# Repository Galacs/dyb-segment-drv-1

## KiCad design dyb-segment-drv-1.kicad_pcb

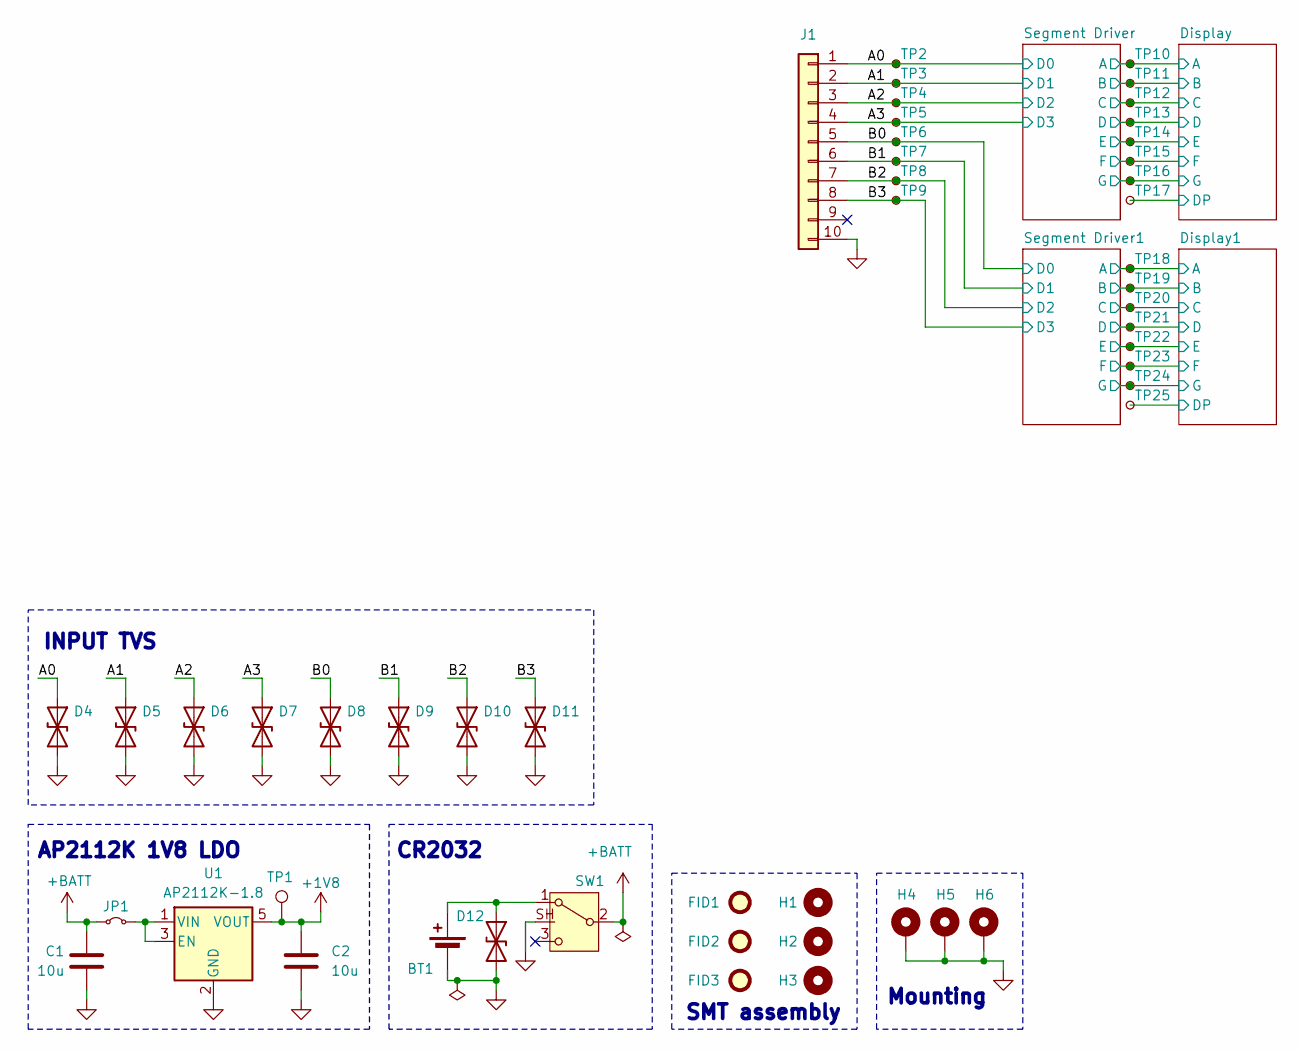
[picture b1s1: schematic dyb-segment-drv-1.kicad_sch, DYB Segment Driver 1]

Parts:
BT1: Battery_Cell; BatteryHolder_MYOUNG_BS-08-B2AA016; Manufacturer Part Number BS-08-B2AA016; JLCPCB Part # C964792
C1, C2: 10u; C_0805_2012Metric; Manufacturer Part Number GRM21BR61H106KE43L; JLCPCB Part # C440198
D4, D5, D6, D7, D8, D9, D10, D11, D12: H3V3L10B; Diode_DFN1006; Manufacturer Part Number H3V3L10B; JLCPCB Part # C20615781
FID1, FID2, FID3: Fiducial; Fiducial_1mm_Mask2mm
H1, H2, H3: MountingHole; ToolingHole_1.152mm
H4, H5, H6: MountingHole_Pad; MountingHole_3.2mm_M3_Pad_Via
J1: Conn_01x10; KYOCERA_AVX9159-006
JP1: Jumper_2_Small_Bridged; PinHeader_1x02_P2.54mm_Horizontal
SW1: SW_SPDT; SW_SPDT_Shouhan_MSK12C02; Manufacturer Part Number MSK12C02; JLCPCB Part # C431540
TP1: TestPoint; TestPoint_Pad_D1.0mm
TP2, TP3, TP4, TP5, TP6, TP7, TP8, TP9, TP10, TP11, TP12, TP13, TP14, TP15, TP16, TP17, TP18, TP19, TP20, TP21, TP22, TP23, TP24, TP25: TestPoint_Small; TestPoint_Pad_D1.0mm
U1: AP2112K-1.8; SOT-23-5; Manufacturer Part Number AP2112K-1.8TRG1; JLCPCB Part # C176944

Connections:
+1V8: C2.1, TP1.1 (1_1), U1.5 (VOUT); also elsewhere on the board
/A0: D4.1 (A1), J1.1, TP2.1 (1_1); also elsewhere on the board
/A1: D5.1 (A1), J1.2, TP3.1 (1_1); also elsewhere on the board
/A2: D6.1 (A1), J1.3, TP4.1 (1_1); also elsewhere on the board
/A3: D7.1 (A1), J1.4, TP5.1 (1_1); also elsewhere on the board
/B0: D8.1 (A1), J1.5, TP6.1 (1_1); also elsewhere on the board
/B1: D9.1 (A1), J1.6, TP7.1 (1_1); also elsewhere on the board
/B2: D10.1 (A1), J1.7, TP8.1 (1_1); also elsewhere on the board
/B3: D11.1 (A1), J1.8, TP9.1 (1_1); also elsewhere on the board
/Display1/A: TP18.1 (1_1); also elsewhere on the board
/Display1/B: TP19.1 (1_1); also elsewhere on the board
/Display1/C: TP20.1 (1_1); also elsewhere on the board
/Display1/D: TP21.1 (1_1); also elsewhere on the board
/Display1/DP: TP25.1 (1_1); also elsewhere on the board
/Display1/E: TP22.1 (1_1); also elsewhere on the board
/Display1/F: TP23.1 (1_1); also elsewhere on the board
/Display1/G: TP24.1 (1_1); also elsewhere on the board
/Display/A: TP10.1 (1_1); also elsewhere on the board
/Display/B: TP11.1 (1_1); also elsewhere on the board
/Display/C: TP12.1 (1_1); also elsewhere on the board
/Display/D: TP13.1 (1_1); also elsewhere on the board
/Display/DP: TP17.1 (1_1); also elsewhere on the board
/Display/E: TP14.1 (1_1); also elsewhere on the board
/Display/F: TP15.1 (1_1); also elsewhere on the board
/Display/G: TP16.1 (1_1); also elsewhere on the board
GND: BT1.2 (-), C1.2, C2.2, D4.2 (A2), D5.2 (A2), D6.2 (A2), D7.2 (A2), D8.2 (A2), D9.2 (A2), D10.2 (A2), D11.2 (A2), D12.2 (A2), H4.1 (1_1), H5.1 (1_1), H6.1 (1_1), J1.10, SW1.SH, U1.2 (GND); also elsewhere on the board
unnamed: BT1.1 (+), D12.1 (A1), SW1.1 (A)

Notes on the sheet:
SMT assembly
INPUT TVS
Mounting
AP2112K 1V8 LDO
CR2032

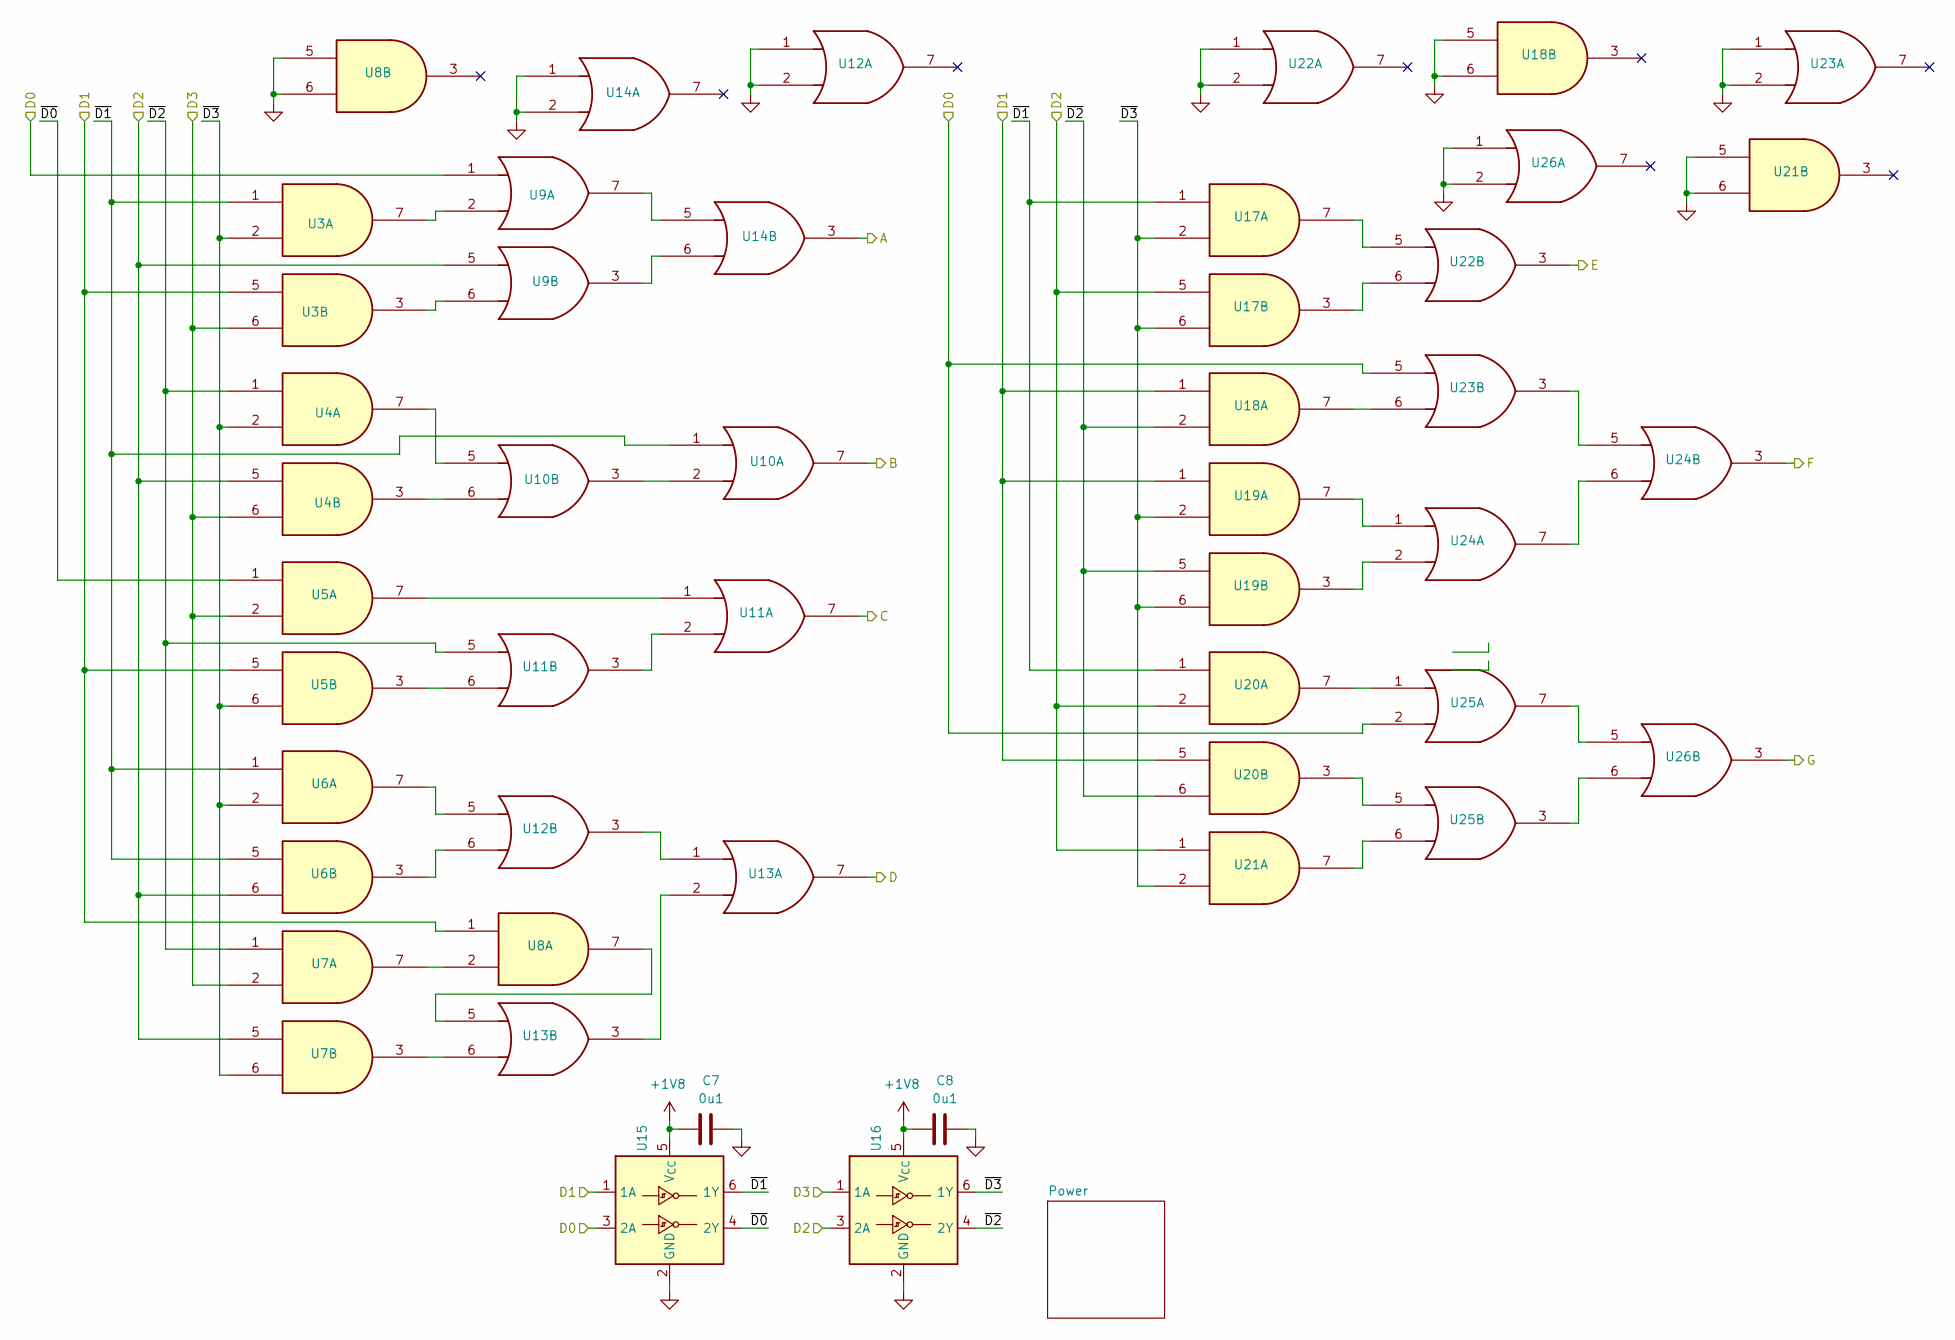
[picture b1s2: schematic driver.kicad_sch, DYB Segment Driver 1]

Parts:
C7, C8: 0u1; C_0402_1005Metric; Manufacturer Part Number CL05B104KB54PNC; JLCPCB Part # C307331
U3, U4, U5, U6, U7, U8, U17, U18, U19, U20, U21: SN74AUP2G08; VSSOP-8_2.3x2mm_P0.5mm; Manufacturer Part Number SN74AUP2G08DCUR; JLCPCB Part # C544478
U9, U10, U11, U12, U13, U14, U22, U23, U24, U25, U26: 74AUC2G32; VSSOP-8_2.3x2mm_P0.5mm; Manufacturer Part Number SN74AUP2G32DCUR; JLCPCB Part # C2876519
U15, U16: Inverter_Schmitt_Dual; SOT-363_SC-70-6; Manufacturer Part Number SN74AUP2G14DCKR; JLCPCB Part # C139318

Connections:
+1V8: C7.1, C8.1, U15.5 (V_{CC}), U16.5 (V_{CC}); also elsewhere on the board
/A0: U9.1, U15.3 (2A), U23.5, U25.2; also elsewhere on the board
/A1: U3.5, U5.5, U8.1, U15.1 (1A), U18.1, U19.1, U20.5; also elsewhere on the board
/A2: U4.5, U6.6, U7.5, U9.5, U16.3 (2A), U17.5, U20.2, U21.1; also elsewhere on the board
/A3: U3.6, U4.6, U5.2, U7.2, U16.1 (1A); also elsewhere on the board
/Display/A: U14.3; also elsewhere on the board
/Display/B: U10.7; also elsewhere on the board
/Display/C: U11.7; also elsewhere on the board
/Display/D: U13.7; also elsewhere on the board
/Display/E: U22.3; also elsewhere on the board
/Display/F: U24.3; also elsewhere on the board
/Display/G: U26.3; also elsewhere on the board
/Segment Driver/~D0: U5.1, U15.4 (2Y)
/Segment Driver/~D1: U3.1, U6.1, U6.5, U10.1, U15.6 (1Y), U17.1, U20.1
/Segment Driver/~D2: U4.1, U7.1, U11.5, U16.4 (2Y), U18.2, U19.5, U20.6
/Segment Driver/~D3: U3.2, U4.2, U5.6, U6.2, U7.6, U16.6 (1Y), U17.2, U17.6, U19.2, U19.6, U21.2
GND: C7.2, C8.2, U8.5, U8.6, U12.1, U12.2, U14.1, U14.2, U15.2 (GND), U16.2 (GND), U18.5, U18.6, U21.5, U21.6, U22.1, U22.2, U23.1, U23.2, U26.1, U26.2; also elsewhere on the board
unnamed: U3.3, U9.6
unnamed: U3.7, U9.2
unnamed: U7.7, U8.2
unnamed: U10.2, U10.3
unnamed: U4.7, U10.5
unnamed: U4.3, U10.6
unnamed: U5.7, U11.1
unnamed: U11.2, U11.3
unnamed: U5.3, U11.6
unnamed: U12.3, U13.1
unnamed: U6.7, U12.5
unnamed: U6.3, U12.6
unnamed: U13.2, U13.3
unnamed: U8.7, U13.5
unnamed: U7.3, U13.6
unnamed: U9.7, U14.5
unnamed: U9.3, U14.6
unnamed: U17.3, U22.6
unnamed: U17.7, U22.5
unnamed: U18.7, U23.6
unnamed: U19.3, U24.2
unnamed: U19.7, U24.1
unnamed: U20.3, U25.5
unnamed: U20.7, U25.1
unnamed: U21.7, U25.6
unnamed: U23.3, U24.5
unnamed: U24.6, U24.7
unnamed: U25.3, U26.6
unnamed: U25.7, U26.5

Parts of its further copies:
C35, C36: 0u1; C_0402_1005Metric; Manufacturer Part Number CL05B104KB54PNC; JLCPCB Part # C307331
U28, U29, U30, U31, U32, U33, U42, U43, U44, U45, U46: SN74AUP2G08; VSSOP-8_2.3x2mm_P0.5mm; Manufacturer Part Number SN74AUP2G08DCUR; JLCPCB Part # C544478
U34, U35, U36, U37, U38, U39, U47, U48, U49, U50, U51: 74AUC2G32; VSSOP-8_2.3x2mm_P0.5mm; Manufacturer Part Number SN74AUP2G32DCUR; JLCPCB Part # C2876519
U40, U41: Inverter_Schmitt_Dual; SOT-363_SC-70-6; Manufacturer Part Number SN74AUP2G14DCKR; JLCPCB Part # C139318

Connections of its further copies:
+1V8: C35.1, C36.1, U28.8 (VCC), U29.8 (VCC), U30.8 (VCC), U31.8 (VCC), U32.8 (VCC), U33.8 (VCC), U34.8 (VCC), U35.8 (VCC), U36.8 (VCC), U37.8 (VCC), U38.8 (VCC), U39.8 (VCC), U40.5 (V_{CC}), U41.5 (V_{CC}), U42.8 (VCC), U43.8 (VCC), U44.8 (VCC), U45.8 (VCC), U46.8 (VCC), U47.8 (VCC), U48.8 (VCC), U49.8 (VCC), U50.8 (VCC), U51.8 (VCC); also elsewhere on the board
/B0: U34.1, U40.3 (2A), U48.5, U50.2; also elsewhere on the board
/B1: U28.5, U30.5, U33.1, U40.1 (1A), U43.1, U44.1, U45.5; also elsewhere on the board
/B2: U29.5, U31.6, U32.5, U34.5, U41.3 (2A), U42.5, U45.2, U46.1; also elsewhere on the board
/B3: U28.6, U29.6, U30.2, U32.2, U41.1 (1A); also elsewhere on the board
/Display1/A: U39.3; also elsewhere on the board
/Display1/B: U35.7; also elsewhere on the board
/Display1/C: U36.7; also elsewhere on the board
/Display1/D: U38.7; also elsewhere on the board
/Display1/E: U47.3; also elsewhere on the board
/Display1/F: U49.3; also elsewhere on the board
/Display1/G: U51.3; also elsewhere on the board
/Segment Driver1/~D0: U30.1, U40.4 (2Y)
/Segment Driver1/~D1: U28.1, U31.1, U31.5, U35.1, U40.6 (1Y), U42.1, U45.1
/Segment Driver1/~D2: U29.1, U32.1, U36.5, U41.4 (2Y), U43.2, U44.5, U45.6
/Segment Driver1/~D3: U28.2, U29.2, U30.6, U31.2, U32.6, U41.6 (1Y), U42.2, U42.6, U44.2, U44.6, U46.2
GND: C35.2, C36.2, U28.4 (GND), U29.4 (GND), U30.4 (GND), U31.4 (GND), U32.4 (GND), U33.4 (GND), U33.5, U33.6, U34.4 (GND), U35.4 (GND), U36.4 (GND), U37.1, U37.2, U37.4 (GND), U38.4 (GND), U39.1, U39.2, U39.4 (GND), U40.2 (GND), U41.2 (GND), U42.4 (GND), U43.4 (GND), U43.5, U43.6, U44.4 (GND), U45.4 (GND), U46.4 (GND), U46.5, U46.6, U47.1, U47.2, U47.4 (GND), U48.1, U48.2, U48.4 (GND), U49.4 (GND), U50.4 (GND), U51.1, U51.2, U51.4 (GND); also elsewhere on the board
unnamed: U28.3, U34.6
unnamed: U28.7, U34.2
unnamed: U29.3, U35.6
unnamed: U29.7, U35.5
unnamed: U30.3, U36.6
unnamed: U30.7, U36.1
unnamed: U31.3, U37.6
unnamed: U31.7, U37.5
unnamed: U32.3, U38.6
unnamed: U32.7, U33.2
unnamed: U33.7, U38.5
unnamed: U34.3, U39.6
unnamed: U34.7, U39.5
unnamed: U35.2, U35.3
unnamed: U36.2, U36.3
unnamed: U37.3, U38.1
unnamed: U38.2, U38.3
unnamed: U42.3, U47.6
unnamed: U42.7, U47.5
unnamed: U43.7, U48.6
unnamed: U44.3, U49.2
unnamed: U44.7, U49.1
unnamed: U45.3, U50.5
unnamed: U45.7, U50.1
unnamed: U46.7, U50.6
unnamed: U48.3, U49.5
unnamed: U49.6, U49.7
unnamed: U50.3, U51.6
unnamed: U50.7, U51.5

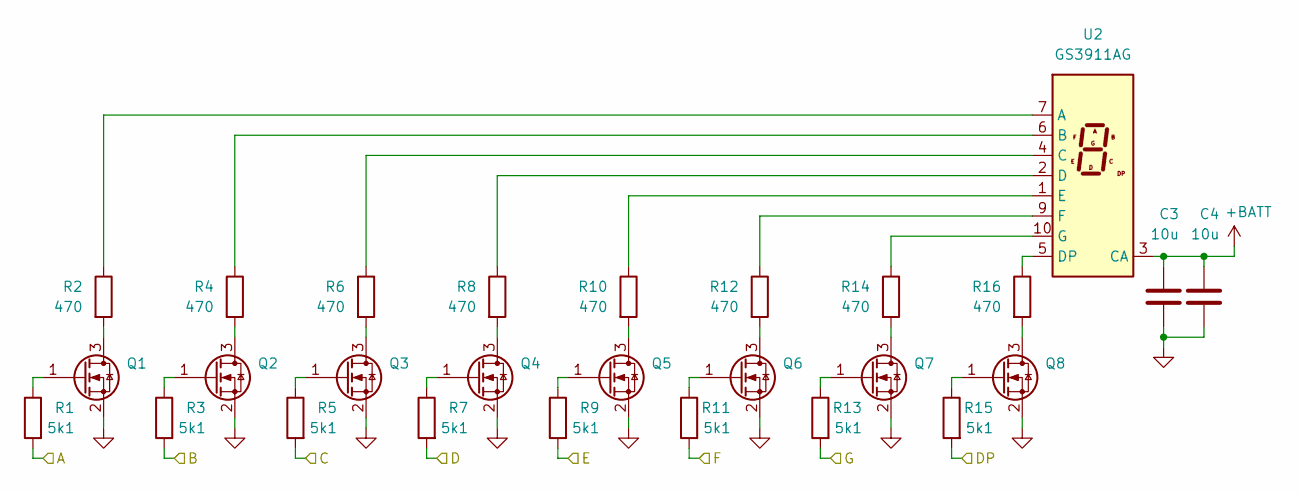
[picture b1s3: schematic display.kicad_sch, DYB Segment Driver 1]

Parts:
C3, C4: 10u; C_0805_2012Metric; Manufacturer Part Number GRM21BR61H106KE43L; JLCPCB Part # C440198
Q1, Q2, Q3, Q4, Q5, Q6, Q7, Q8: HL2300; SOT-23; Manufacturer Part Number HL2300; JLCPCB Part # C7420343
R1, R3, R5, R7, R9, R11, R13, R15: 5k1; R_0402_1005Metric; Manufacturer Part Number 0402WGF5101TCE; JLCPCB Part # C25905
R2, R4, R6, R8, R10, R12, R14, R16: 470; R_0402_1005Metric; Manufacturer Part Number 0402WGF4700TCE; JLCPCB Part # C25117
U2: GS3911AG; Manufacturer Part Number GS3911AG-G; JLCPCB Part # C22462667

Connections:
/Display/A: R1.2; also elsewhere on the board
/Display/B: R3.2; also elsewhere on the board
/Display/C: R5.2; also elsewhere on the board
/Display/D: R7.2; also elsewhere on the board
/Display/DP: R15.2; also elsewhere on the board
/Display/E: R9.2; also elsewhere on the board
/Display/F: R11.2; also elsewhere on the board
/Display/G: R13.2; also elsewhere on the board
GND: C3.2, C4.2, Q1.2 (S), Q2.2 (S), Q3.2 (S), Q4.2 (S), Q5.2 (S), Q6.2 (S), Q7.2 (S), Q8.2 (S); also elsewhere on the board
unnamed: Q1.3 (D), R2.2
unnamed: Q1.1 (G), R1.1
unnamed: Q2.3 (D), R4.2
unnamed: Q2.1 (G), R3.1
unnamed: Q3.3 (D), R6.2
unnamed: Q3.1 (G), R5.1
unnamed: Q4.3 (D), R8.2
unnamed: Q4.1 (G), R7.1
unnamed: Q5.3 (D), R10.2
unnamed: Q5.1 (G), R9.1
unnamed: Q6.3 (D), R12.2
unnamed: Q6.1 (G), R11.1
unnamed: Q7.3 (D), R14.2
unnamed: Q7.1 (G), R13.1
unnamed: Q8.3 (D), R16.2
unnamed: Q8.1 (G), R15.1
unnamed: R2.1, U2.7 (A)
unnamed: R4.1, U2.6 (B)
unnamed: R6.1, U2.4 (C)
unnamed: R8.1, U2.2 (D)
unnamed: R16.1, U2.5 (DP)
unnamed: R10.1, U2.1 (E)
unnamed: R12.1, U2.9 (F)
unnamed: R14.1, U2.10 (G)

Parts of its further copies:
C5, C31: 10u; C_0805_2012Metric; Manufacturer Part Number GRM21BR61H106KE43L; JLCPCB Part # C440198
Q9, Q10, Q11, Q12, Q13, Q14, Q15, Q16: HL2300; SOT-23; Manufacturer Part Number HL2300; JLCPCB Part # C7420343
R17, R19, R21, R23, R25, R27, R29, R31: 5k1; R_0402_1005Metric; Manufacturer Part Number 0402WGF5101TCE; JLCPCB Part # C25905
R18, R20, R22, R24, R26, R28, R30, R32: 470; R_0402_1005Metric; Manufacturer Part Number 0402WGF4700TCE; JLCPCB Part # C25117
U27: GS3911AG; Manufacturer Part Number GS3911AG-G; JLCPCB Part # C22462667

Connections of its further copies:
/Display1/A: R17.2; also elsewhere on the board
/Display1/B: R19.2; also elsewhere on the board
/Display1/C: R21.2; also elsewhere on the board
/Display1/D: R23.2; also elsewhere on the board
/Display1/DP: R31.2; also elsewhere on the board
/Display1/E: R25.2; also elsewhere on the board
/Display1/F: R27.2; also elsewhere on the board
/Display1/G: R29.2; also elsewhere on the board
GND: C5.2, C31.2, Q9.2 (S), Q10.2 (S), Q11.2 (S), Q12.2 (S), Q13.2 (S), Q14.2 (S), Q15.2 (S), Q16.2 (S); also elsewhere on the board
unnamed: Q9.3 (D), R18.2
unnamed: Q9.1 (G), R17.1
unnamed: Q10.3 (D), R20.2
unnamed: Q10.1 (G), R19.1
unnamed: Q11.3 (D), R22.2
unnamed: Q11.1 (G), R21.1
unnamed: Q12.3 (D), R24.2
unnamed: Q12.1 (G), R23.1
unnamed: Q13.3 (D), R26.2
unnamed: Q13.1 (G), R25.1
unnamed: Q14.3 (D), R28.2
unnamed: Q14.1 (G), R27.1
unnamed: Q15.3 (D), R30.2
unnamed: Q15.1 (G), R29.1
unnamed: Q16.3 (D), R32.2
unnamed: Q16.1 (G), R31.1
unnamed: R18.1, U27.7 (A)
unnamed: R20.1, U27.6 (B)
unnamed: R22.1, U27.4 (C)
unnamed: R24.1, U27.2 (D)
unnamed: R32.1, U27.5 (DP)
unnamed: R26.1, U27.1 (E)
unnamed: R28.1, U27.9 (F)
unnamed: R30.1, U27.10 (G)

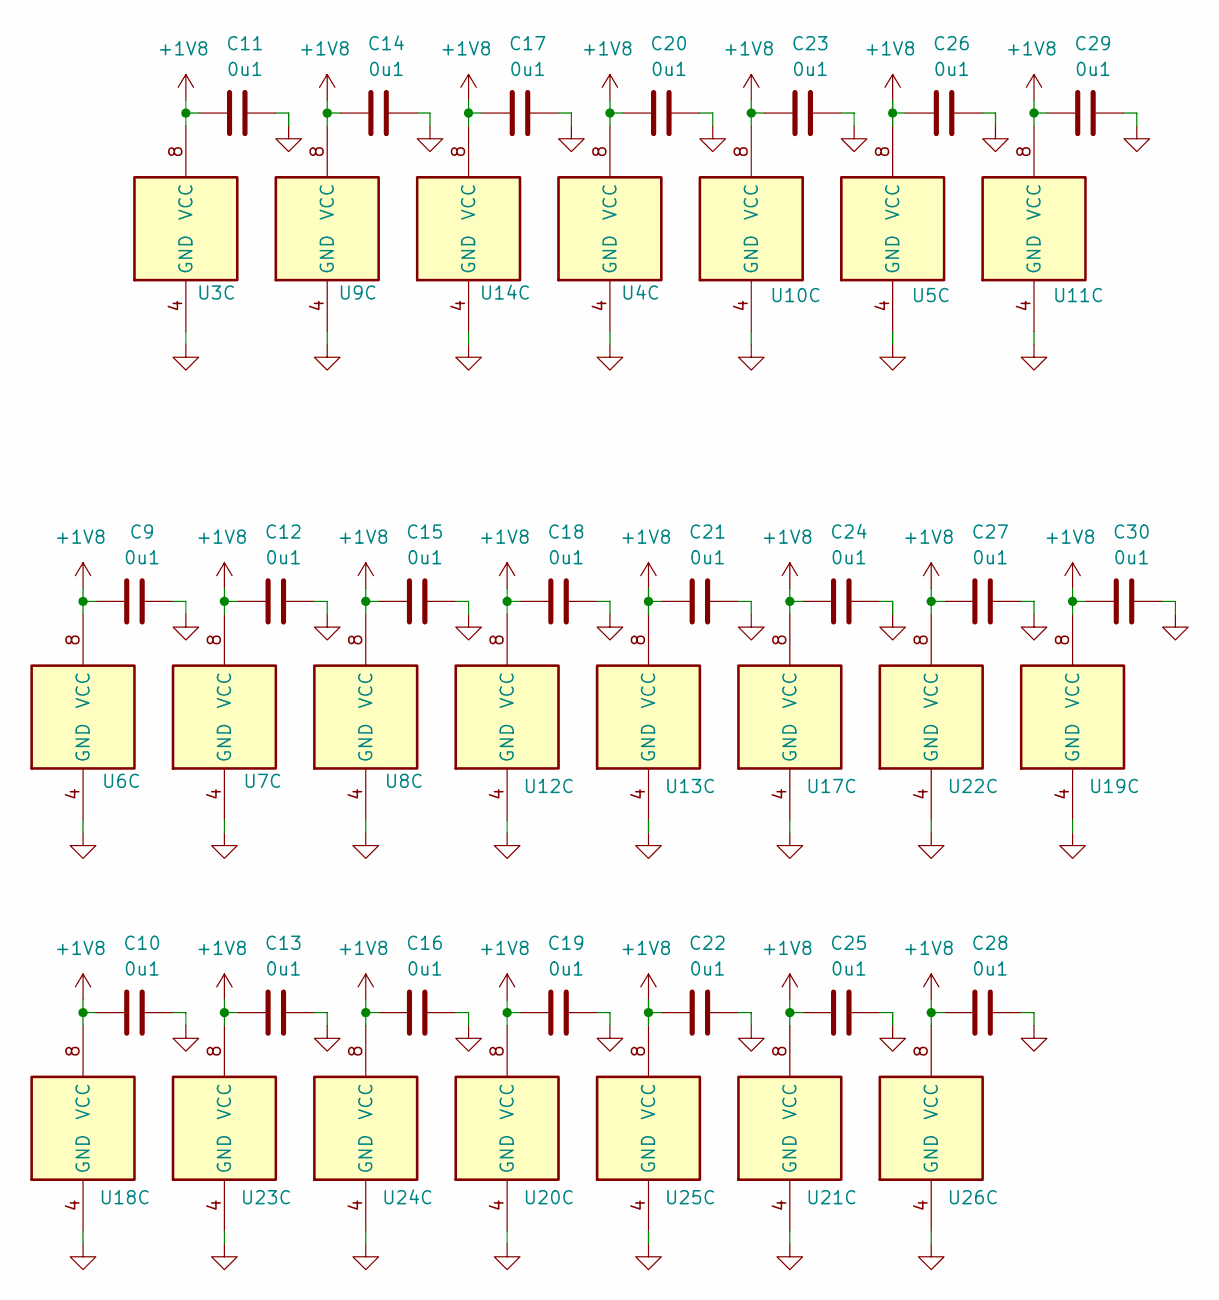
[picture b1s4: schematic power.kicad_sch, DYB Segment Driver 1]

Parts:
C9, C10, C11, C12, C13, C14, C15, C16, C17, C18, C19, C20, C21, C22, C23, C24, C25, C26, C27, C28, C29, C30: 0u1; C_0402_1005Metric; Manufacturer Part Number CL05B104KB54PNC; JLCPCB Part # C307331
U3, U4, U5, U6, U7, U8, U17, U18, U19, U20, U21: SN74AUP2G08; VSSOP-8_2.3x2mm_P0.5mm; Manufacturer Part Number SN74AUP2G08DCUR; JLCPCB Part # C544478
U9, U10, U11, U12, U13, U14, U22, U23, U24, U25, U26: 74AUC2G32; VSSOP-8_2.3x2mm_P0.5mm; Manufacturer Part Number SN74AUP2G32DCUR; JLCPCB Part # C2876519

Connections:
+1V8: C9.1, C10.1, C11.1, C12.1, C13.1, C14.1, C15.1, C16.1, C17.1, C18.1, C19.1, C20.1, C21.1, C22.1, C23.1, C24.1, C25.1, C26.1, C27.1, C28.1, C29.1, C30.1, U3.8 (VCC), U4.8 (VCC), U5.8 (VCC), U6.8 (VCC), U7.8 (VCC), U8.8 (VCC), U9.8 (VCC), U10.8 (VCC), U11.8 (VCC), U12.8 (VCC), U13.8 (VCC), U14.8 (VCC), U17.8 (VCC), U18.8 (VCC), U19.8 (VCC), U20.8 (VCC), U21.8 (VCC), U22.8 (VCC), U23.8 (VCC), U24.8 (VCC), U25.8 (VCC), U26.8 (VCC); also elsewhere on the board
GND: C9.2, C10.2, C11.2, C12.2, C13.2, C14.2, C15.2, C16.2, C17.2, C18.2, C19.2, C20.2, C21.2, C22.2, C23.2, C24.2, C25.2, C26.2, C27.2, C28.2, C29.2, C30.2, U3.4 (GND), U4.4 (GND), U5.4 (GND), U6.4 (GND), U7.4 (GND), U8.4 (GND), U9.4 (GND), U10.4 (GND), U11.4 (GND), U12.4 (GND), U13.4 (GND), U14.4 (GND), U17.4 (GND), U18.4 (GND), U19.4 (GND), U20.4 (GND), U21.4 (GND), U22.4 (GND), U23.4 (GND), U24.4 (GND), U25.4 (GND), U26.4 (GND); also elsewhere on the board

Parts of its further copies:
C37, C38, C39, C40, C41, C42, C43, C44, C45, C46, C47, C48, C49, C50, C51, C52, C53, C54, C55, C56, C57, C58: 0u1; C_0402_1005Metric; Manufacturer Part Number CL05B104KB54PNC; JLCPCB Part # C307331
U28, U29, U30, U31, U32, U33, U42, U43, U44, U45, U46: SN74AUP2G08; VSSOP-8_2.3x2mm_P0.5mm; Manufacturer Part Number SN74AUP2G08DCUR; JLCPCB Part # C544478
U34, U35, U36, U37, U38, U39, U47, U48, U49, U50, U51: 74AUC2G32; VSSOP-8_2.3x2mm_P0.5mm; Manufacturer Part Number SN74AUP2G32DCUR; JLCPCB Part # C2876519

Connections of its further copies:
+1V8: C37.1, C38.1, C39.1, C40.1, C41.1, C42.1, C43.1, C44.1, C45.1, C46.1, C47.1, C48.1, C49.1, C50.1, C51.1, C52.1, C53.1, C54.1, C55.1, C56.1, C57.1, C58.1, U28.8 (VCC), U29.8 (VCC), U30.8 (VCC), U31.8 (VCC), U32.8 (VCC), U33.8 (VCC), U34.8 (VCC), U35.8 (VCC), U36.8 (VCC), U37.8 (VCC), U38.8 (VCC), U39.8 (VCC), U42.8 (VCC), U43.8 (VCC), U44.8 (VCC), U45.8 (VCC), U46.8 (VCC), U47.8 (VCC), U48.8 (VCC), U49.8 (VCC), U50.8 (VCC), U51.8 (VCC); also elsewhere on the board
/B0: U34.1, U48.5, U50.2; also elsewhere on the board
/B1: U28.5, U30.5, U33.1, U43.1, U44.1, U45.5; also elsewhere on the board
/B2: U29.5, U31.6, U32.5, U34.5, U42.5, U45.2, U46.1; also elsewhere on the board
/B3: U28.6, U29.6, U30.2, U32.2; also elsewhere on the board
/Display1/A: U39.3; also elsewhere on the board
/Display1/B: U35.7; also elsewhere on the board
/Display1/C: U36.7; also elsewhere on the board
/Display1/D: U38.7; also elsewhere on the board
/Display1/E: U47.3; also elsewhere on the board
/Display1/F: U49.3; also elsewhere on the board
/Display1/G: U51.3; also elsewhere on the board
/Segment Driver1/~D0: U30.1; also elsewhere on the board
/Segment Driver1/~D1: U28.1, U31.1, U31.5, U35.1, U42.1, U45.1; also elsewhere on the board
/Segment Driver1/~D2: U29.1, U32.1, U36.5, U43.2, U44.5, U45.6; also elsewhere on the board
/Segment Driver1/~D3: U28.2, U29.2, U30.6, U31.2, U32.6, U42.2, U42.6, U44.2, U44.6, U46.2; also elsewhere on the board
GND: C37.2, C38.2, C39.2, C40.2, C41.2, C42.2, C43.2, C44.2, C45.2, C46.2, C47.2, C48.2, C49.2, C50.2, C51.2, C52.2, C53.2, C54.2, C55.2, C56.2, C57.2, C58.2, U28.4 (GND), U29.4 (GND), U30.4 (GND), U31.4 (GND), U32.4 (GND), U33.4 (GND), U33.5, U33.6, U34.4 (GND), U35.4 (GND), U36.4 (GND), U37.1, U37.2, U37.4 (GND), U38.4 (GND), U39.1, U39.2, U39.4 (GND), U42.4 (GND), U43.4 (GND), U43.5, U43.6, U44.4 (GND), U45.4 (GND), U46.4 (GND), U46.5, U46.6, U47.1, U47.2, U47.4 (GND), U48.1, U48.2, U48.4 (GND), U49.4 (GND), U50.4 (GND), U51.1, U51.2, U51.4 (GND); also elsewhere on the board
unnamed: U28.3, U34.6
unnamed: U28.7, U34.2
unnamed: U29.3, U35.6
unnamed: U29.7, U35.5
unnamed: U30.3, U36.6
unnamed: U30.7, U36.1
unnamed: U31.3, U37.6
unnamed: U31.7, U37.5
unnamed: U32.3, U38.6
unnamed: U32.7, U33.2
unnamed: U33.7, U38.5
unnamed: U34.3, U39.6
unnamed: U34.7, U39.5
unnamed: U35.2, U35.3
unnamed: U36.2, U36.3
unnamed: U37.3, U38.1
unnamed: U38.2, U38.3
unnamed: U42.3, U47.6
unnamed: U42.7, U47.5
unnamed: U43.7, U48.6
unnamed: U44.3, U49.2
unnamed: U44.7, U49.1
unnamed: U45.3, U50.5
unnamed: U45.7, U50.1
unnamed: U46.7, U50.6
unnamed: U48.3, U49.5
unnamed: U49.6, U49.7
unnamed: U50.3, U51.6
unnamed: U50.7, U51.5

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
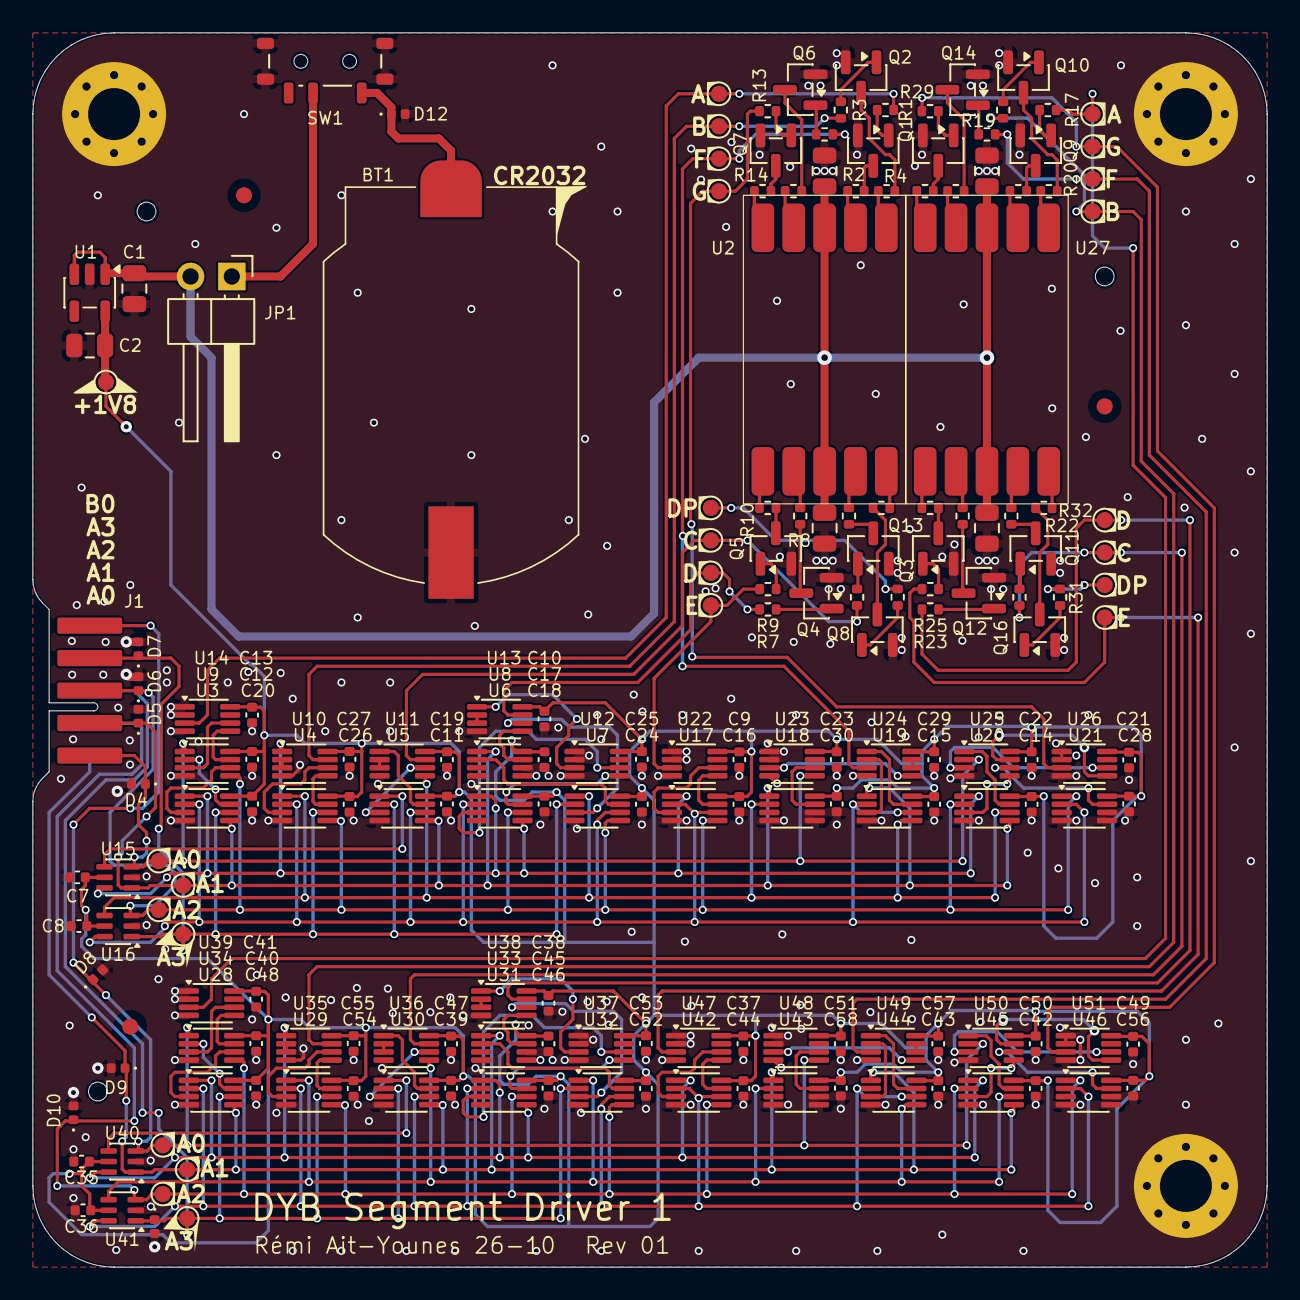
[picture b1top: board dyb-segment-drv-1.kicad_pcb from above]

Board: 2 copper layers, 76.0 x 76.0 mm, 200 parts (0 on the bottom side), 142 nets.

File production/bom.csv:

Designator,Footprint,Quantity,Value,LCSC Part #
BT1,BatteryHolder_MYOUNG_BS-08-B2AA016,1,Battery_Cell,C964792
"C1, C2, C3, C31, C4, C5",0805,6,10u,C440198
"C10, C11, C12, C13, C14, C15, C16, C17, C18, C19, C20, C21, C22, C23, C24, C25, C26, C27, C28, C29, C30, C35, C36, C37, C38, C39, C40, C41, C42, C43, C44, C45, C46, C47, C48, C49, C50, C51, C52, C53, C54, C55, C56, C57, C58, C7, C8, C9",0402,48,0u1,C307331
"D10, D11, D12, D4, D5, D6, D7, D8, D9",Diode_DFN1006,9,H3V3L10B,C20615781
J1,KYOCERA_AVX9159-006,1,Conn_01x10,
"Q1, Q10, Q11, Q12, Q13, Q14, Q15, Q16, Q2, Q3, Q4, Q5, Q6, Q7, Q8, Q9",SOT-23,16,HL2300,C7420343
"R1, R11, R13, R15, R17, R19, R21, R23, R25, R27, R29, R3, R31, R5, R7, R9",0402,16,5k1,C25905
"R10, R12, R14, R16, R18, R2, R20, R22, R24, R26, R28, R30, R32, R4, R6, R8",0402,16,470,C25117
SW1,SW_SPDT_Shouhan_MSK12C02,1,SW_SPDT,C431540
U1,SOT-23-5,1,AP2112K-1.8,C176944
"U10, U11, U12, U13, U14, U22, U23, U24, U25, U26, U34, U35, U36, U37, U38, U39, U47, U48, U49, U50, U51, U9",VSSOP-8_2.3x2mm_P0.5mm,22,74AUC2G32,C2876519
"U15, U16, U40, U41",SOT-363_SC-70-6,4,Inverter_Schmitt_Dual,C139318
"U17, U18, U19, U20, U21, U28, U29, U3, U30, U31, U32, U33, U4, U42, U43, U44, U45, U46, U5, U6, U7, U8",VSSOP-8_2.3x2mm_P0.5mm,22,SN74AUP2G08,C544478
"U2, U27",GS3911AG,2,GS3911AG,C22462667
